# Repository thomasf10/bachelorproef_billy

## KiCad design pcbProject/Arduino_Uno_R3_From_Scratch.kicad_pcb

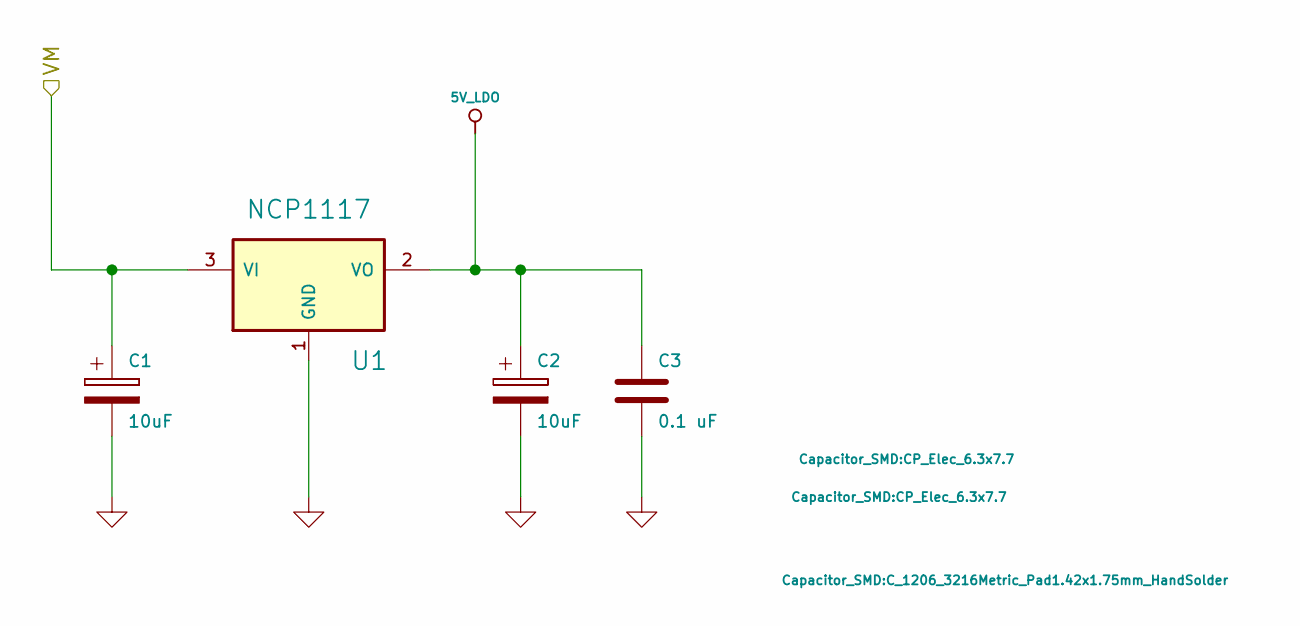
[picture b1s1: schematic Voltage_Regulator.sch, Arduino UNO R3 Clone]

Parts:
C1, C2: 10uF; CP_Elec_6.3x7.7
C3: 0.1 uF; C_1206_3216Metric_Pad1.42x1.75mm_HandSolder
U1: NCP1117; SOT223

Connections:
5V_LDO: C2.1, C3.1, U1.2 (VO); also elsewhere on the board
/DecouplingCapacitors/VM: C1.1, U1.3 (VI); also elsewhere on the board
GND: C1.2, C2.2, C3.2, U1.1 (GND); also elsewhere on the board

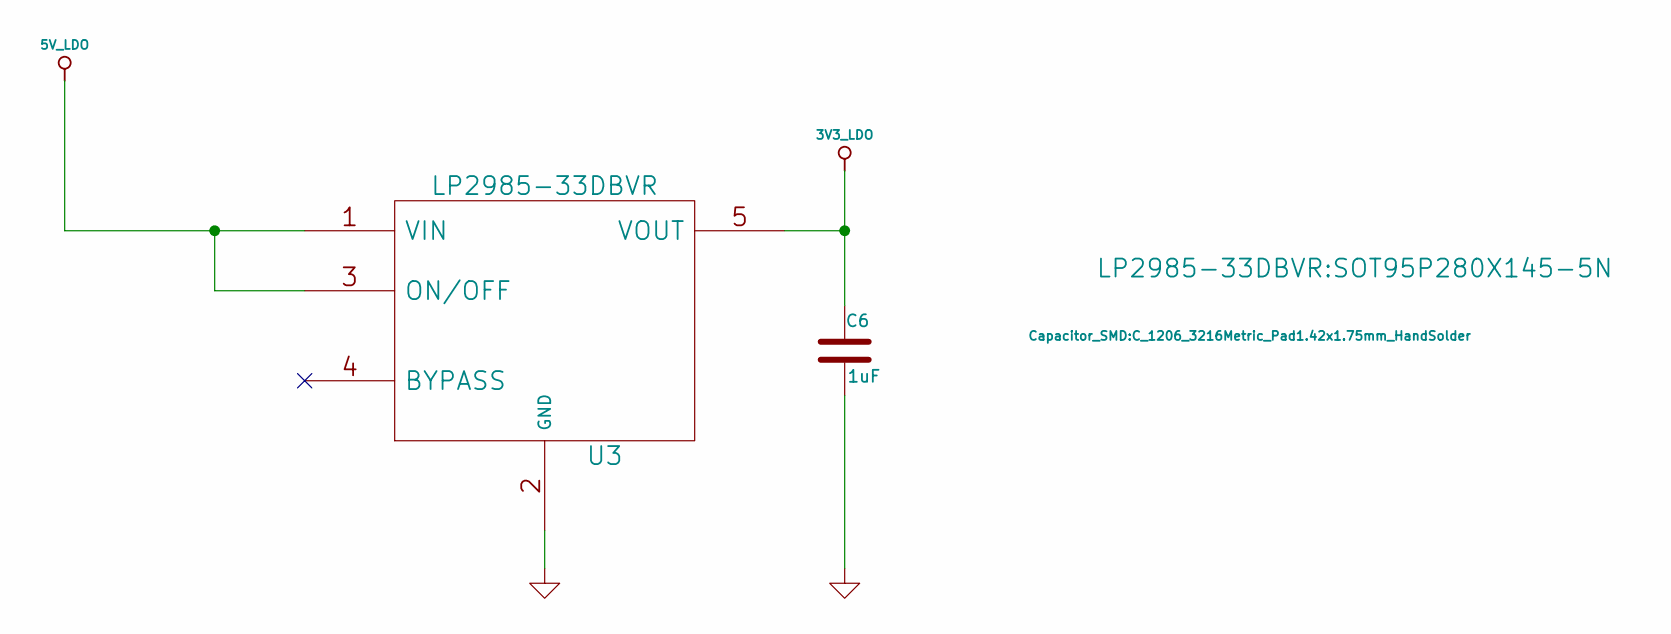
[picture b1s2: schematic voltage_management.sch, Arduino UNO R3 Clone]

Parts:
C6: 1uF; C_1206_3216Metric_Pad1.42x1.75mm_HandSolder
U3: LP2985-33DBVR; SOT95P280X145-5N

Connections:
3V3_LDO: C6.1, U3.5 (VOUT); also elsewhere on the board
5V_LDO: U3.1 (VIN), U3.3 (ON/OFF); also elsewhere on the board
GND: C6.2, U3.2 (GND); also elsewhere on the board

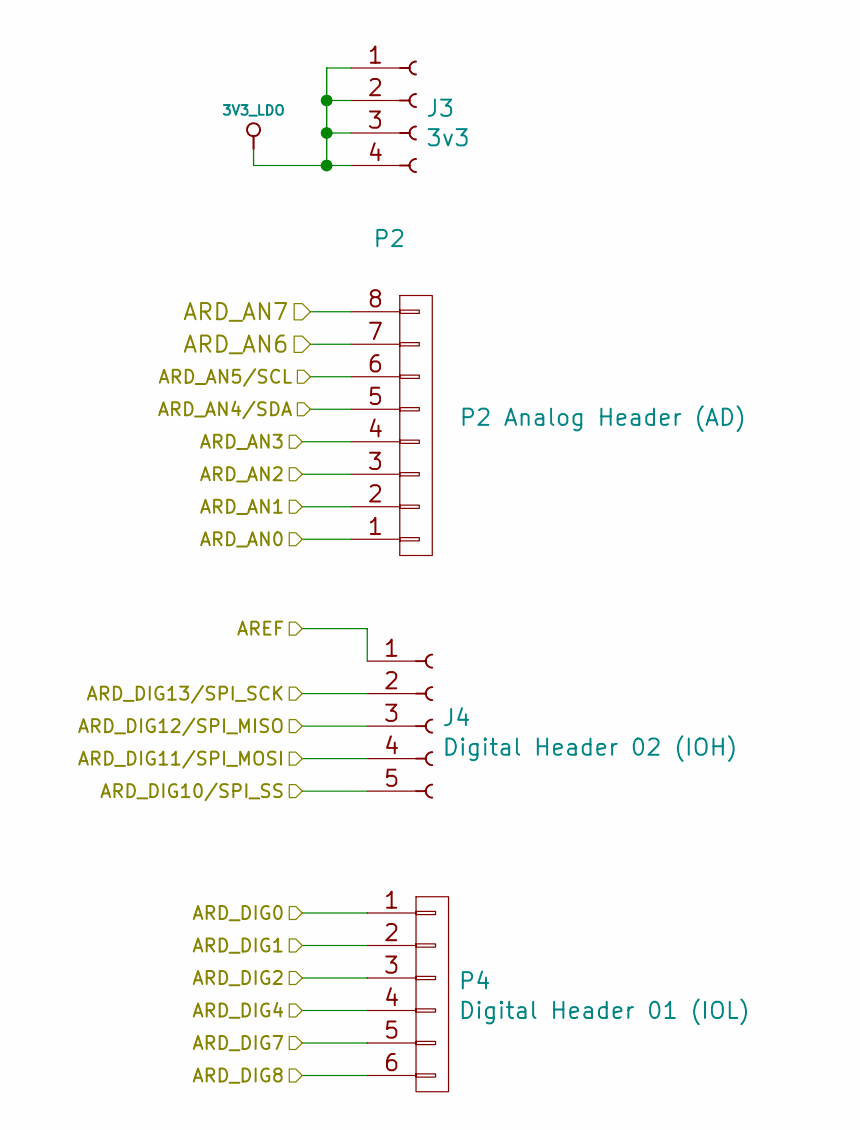
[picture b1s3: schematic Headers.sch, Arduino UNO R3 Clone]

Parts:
J3: 3v3; PinSocket_1x04_P2.54mm_Vertical
J4: Digital Header 02 (IOH); PinSocket_1x05_P2.54mm_Vertical
P2: P2 Analog Header (AD); PinSocket_1x08_P2.54mm_Vertical
P4: Digital Header 01 (IOL); PinSocket_1x06_P2.54mm_Vertical

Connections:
3V3_LDO: J3.1, J3.2, J3.3, J3.4; also elsewhere on the board
328P_ICSP_MISO: J4.3; also elsewhere on the board
328P_ICSP_MOSI: J4.4; also elsewhere on the board
328P_ICSP_SCK: J4.2; also elsewhere on the board
/ATMEGA328P/ARD_AN0: P2.1; also elsewhere on the board
/ATMEGA328P/ARD_AN1: P2.2; also elsewhere on the board
/ATMEGA328P/ARD_AN2: P2.3; also elsewhere on the board
/ATMEGA328P/ARD_AN3: P2.4; also elsewhere on the board
/ATMEGA328P/ARD_AN4/SDA: P2.5; also elsewhere on the board
/ATMEGA328P/ARD_AN5/SCL: P2.6; also elsewhere on the board
/ATMEGA328P/ARD_AN6: P2.7; also elsewhere on the board
/ATMEGA328P/ARD_AN7: P2.8; also elsewhere on the board
/ATMEGA328P/ARD_DIG0: P4.1; also elsewhere on the board
/ATMEGA328P/ARD_DIG1: P4.2; also elsewhere on the board
/ATMEGA328P/ARD_DIG2: P4.3; also elsewhere on the board
/ATMEGA328P/ARD_DIG4: P4.4; also elsewhere on the board
/ATMEGA328P/ARD_DIG7: P4.5; also elsewhere on the board
/ATMEGA328P/ARD_DIG8: P4.6; also elsewhere on the board
/ATMEGA328P/ARD_DIG10/SPI_SS: J4.5; also elsewhere on the board
/ATMEGA328P/AREF: J4.1; also elsewhere on the board

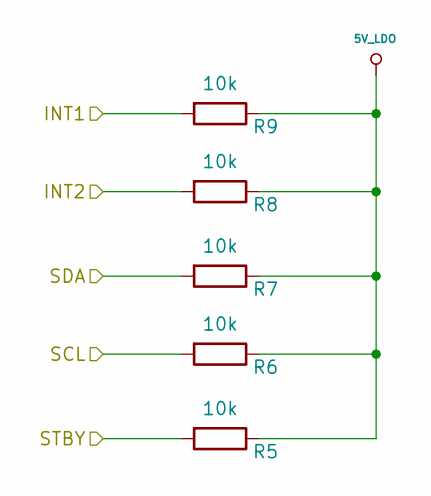
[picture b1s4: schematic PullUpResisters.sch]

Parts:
R5, R6, R7, R8, R9: 10k; R_1206_3216Metric_Pad1.42x1.75mm_HandSolder

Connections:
5V_LDO: R5.1, R6.1, R7.1, R8.1, R9.1; also elsewhere on the board
/ATMEGA328P/ARD_AN4/SDA: R7.2; also elsewhere on the board
/ATMEGA328P/ARD_AN5/SCL: R6.2; also elsewhere on the board
/IOExpander/INT1: R9.2; also elsewhere on the board
/IOExpander/INT2: R8.2; also elsewhere on the board
/MotorDriver/STBY: R5.2; also elsewhere on the board

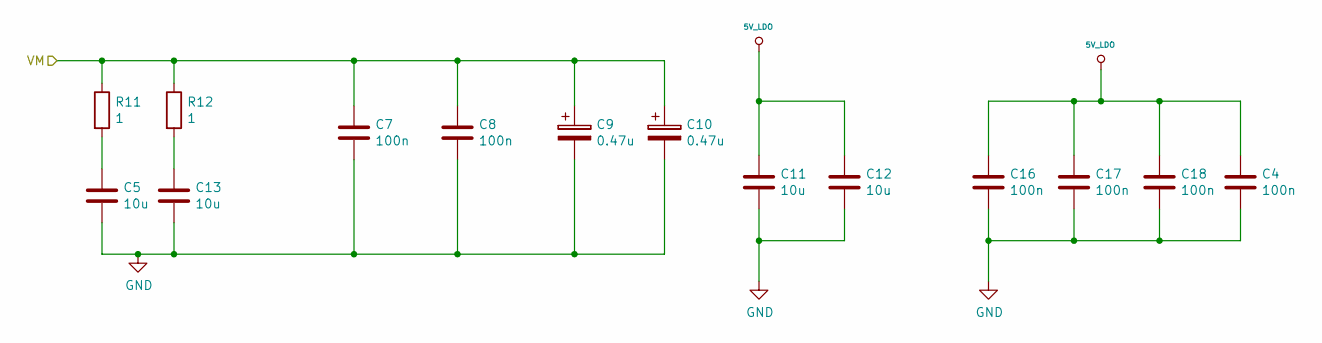
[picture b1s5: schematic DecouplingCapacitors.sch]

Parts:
C4, C7, C8, C16, C17, C18: 100n; C_1206_3216Metric_Pad1.42x1.75mm_HandSolder
C5, C11, C12, C13: 10u; C_1206_3216Metric_Pad1.42x1.75mm_HandSolder
C9, C10: 0.47u; CP_Elec_4x3.9
R11, R12: 1; R_1206_3216Metric_Pad1.42x1.75mm_HandSolder

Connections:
5V_LDO: C4.1, C11.1, C12.1, C16.1, C17.1, C18.1; also elsewhere on the board
/DecouplingCapacitors/VM: C7.1, C8.1, C9.1, C10.1, R11.1, R12.1; also elsewhere on the board
GND: C4.2, C5.2, C7.2, C8.2, C9.2, C10.2, C11.2, C12.2, C13.2, C16.2, C17.2, C18.2; also elsewhere on the board
unnamed: C5.1, R11.2
unnamed: C13.1, R12.2

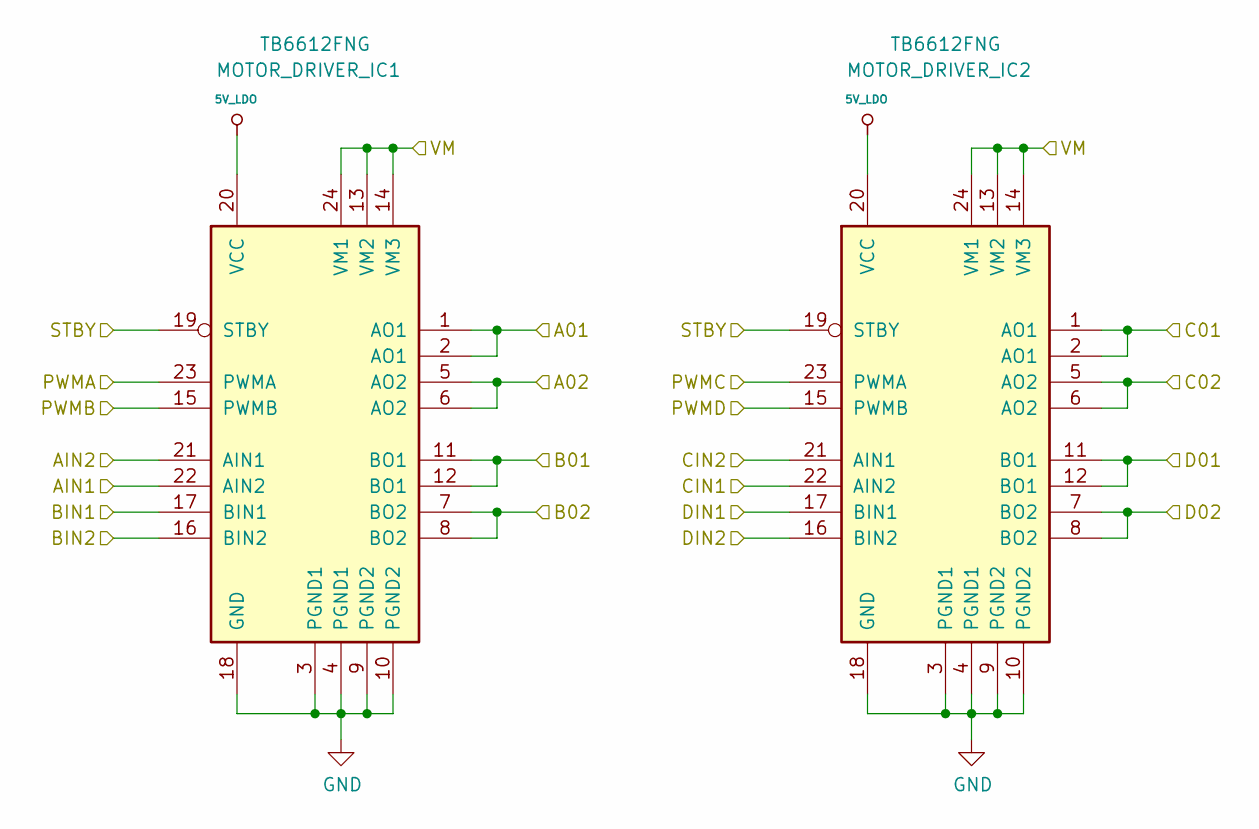
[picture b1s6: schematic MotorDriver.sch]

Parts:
MOTOR_DRIVER_IC1, MOTOR_DRIVER_IC2: TB6612FNG; SSOP-24_5.3x8.2mm_P0.65mm

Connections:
5V_LDO: MOTOR_DRIVER_IC1.20 (VCC), MOTOR_DRIVER_IC2.20 (VCC); also elsewhere on the board
/ATMEGA328P/ARD_DIG3: MOTOR_DRIVER_IC2.15 (PWMB); also elsewhere on the board
/ATMEGA328P/ARD_DIG5: MOTOR_DRIVER_IC2.23 (PWMA); also elsewhere on the board
/ATMEGA328P/ARD_DIG6: MOTOR_DRIVER_IC1.15 (PWMB); also elsewhere on the board
/ATMEGA328P/ARD_DIG9: MOTOR_DRIVER_IC1.23 (PWMA); also elsewhere on the board
/DecouplingCapacitors/VM: MOTOR_DRIVER_IC1.13 (VM2), MOTOR_DRIVER_IC1.14 (VM3), MOTOR_DRIVER_IC1.24 (VM1), MOTOR_DRIVER_IC2.13 (VM2), MOTOR_DRIVER_IC2.14 (VM3), MOTOR_DRIVER_IC2.24 (VM1); also elsewhere on the board
/IOExpander/AIN1: MOTOR_DRIVER_IC1.22 (AIN2); also elsewhere on the board
/IOExpander/AIN2: MOTOR_DRIVER_IC1.21 (AIN1); also elsewhere on the board
/IOExpander/BIN1: MOTOR_DRIVER_IC1.17 (BIN1); also elsewhere on the board
/IOExpander/BIN2: MOTOR_DRIVER_IC1.16 (BIN2); also elsewhere on the board
/IOExpander/CIN1: MOTOR_DRIVER_IC2.22 (AIN2); also elsewhere on the board
/IOExpander/CIN2: MOTOR_DRIVER_IC2.21 (AIN1); also elsewhere on the board
/IOExpander/DIN1: MOTOR_DRIVER_IC2.17 (BIN1); also elsewhere on the board
/IOExpander/DIN2: MOTOR_DRIVER_IC2.16 (BIN2); also elsewhere on the board
/MotorDriver/A01: MOTOR_DRIVER_IC1.1 (AO1), MOTOR_DRIVER_IC1.2 (AO1); also elsewhere on the board
/MotorDriver/A02: MOTOR_DRIVER_IC1.5 (AO2), MOTOR_DRIVER_IC1.6 (AO2); also elsewhere on the board
/MotorDriver/B01: MOTOR_DRIVER_IC1.11 (BO1), MOTOR_DRIVER_IC1.12 (BO1); also elsewhere on the board
/MotorDriver/B02: MOTOR_DRIVER_IC1.7 (BO2), MOTOR_DRIVER_IC1.8 (BO2); also elsewhere on the board
/MotorDriver/C01: MOTOR_DRIVER_IC2.1 (AO1), MOTOR_DRIVER_IC2.2 (AO1); also elsewhere on the board
/MotorDriver/C02: MOTOR_DRIVER_IC2.5 (AO2), MOTOR_DRIVER_IC2.6 (AO2); also elsewhere on the board
/MotorDriver/D01: MOTOR_DRIVER_IC2.11 (BO1), MOTOR_DRIVER_IC2.12 (BO1); also elsewhere on the board
/MotorDriver/D02: MOTOR_DRIVER_IC2.7 (BO2), MOTOR_DRIVER_IC2.8 (BO2); also elsewhere on the board
/MotorDriver/STBY: MOTOR_DRIVER_IC1.19 (STBY), MOTOR_DRIVER_IC2.19 (STBY); also elsewhere on the board
GND: MOTOR_DRIVER_IC1.3 (PGND1), MOTOR_DRIVER_IC1.4 (PGND1), MOTOR_DRIVER_IC1.9 (PGND2), MOTOR_DRIVER_IC1.10 (PGND2), MOTOR_DRIVER_IC1.18 (GND), MOTOR_DRIVER_IC2.3 (PGND1), MOTOR_DRIVER_IC2.4 (PGND1), MOTOR_DRIVER_IC2.9 (PGND2), MOTOR_DRIVER_IC2.10 (PGND2), MOTOR_DRIVER_IC2.18 (GND); also elsewhere on the board

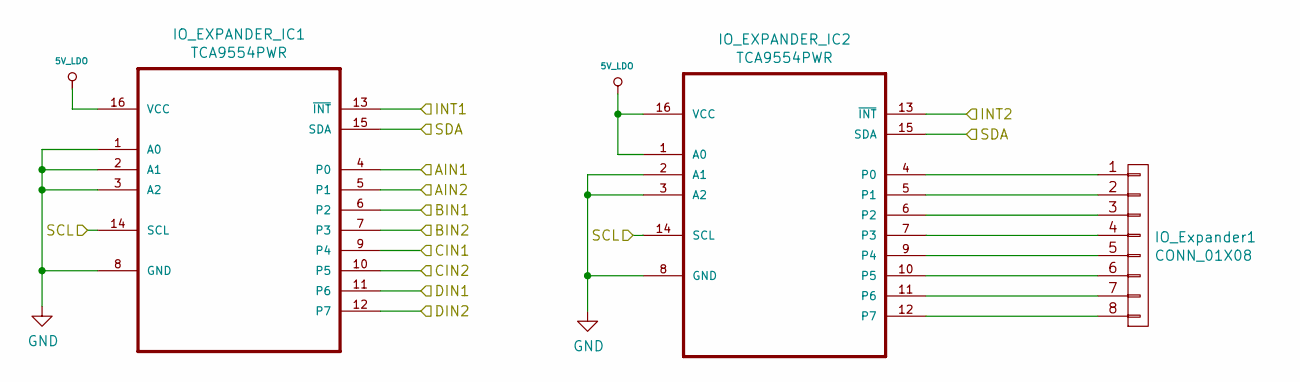
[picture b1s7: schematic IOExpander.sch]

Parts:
IO_EXPANDER_IC1, IO_EXPANDER_IC2: TCA9554PWR; SOP65P640X120-16N
IO_Expander1: CONN_01X08

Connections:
5V_LDO: IO_EXPANDER_IC1.16 (VCC), IO_EXPANDER_IC2.1 (A0), IO_EXPANDER_IC2.16 (VCC); also elsewhere on the board
/ATMEGA328P/ARD_AN4/SDA: IO_EXPANDER_IC1.15 (SDA), IO_EXPANDER_IC2.15 (SDA); also elsewhere on the board
/ATMEGA328P/ARD_AN5/SCL: IO_EXPANDER_IC1.14 (SCL), IO_EXPANDER_IC2.14 (SCL); also elsewhere on the board
/IOExpander/AIN1: IO_EXPANDER_IC1.4 (P0); also elsewhere on the board
/IOExpander/AIN2: IO_EXPANDER_IC1.5 (P1); also elsewhere on the board
/IOExpander/BIN1: IO_EXPANDER_IC1.6 (P2); also elsewhere on the board
/IOExpander/BIN2: IO_EXPANDER_IC1.7 (P3); also elsewhere on the board
/IOExpander/CIN1: IO_EXPANDER_IC1.9 (P4); also elsewhere on the board
/IOExpander/CIN2: IO_EXPANDER_IC1.10 (P5); also elsewhere on the board
/IOExpander/DIN1: IO_EXPANDER_IC1.11 (P6); also elsewhere on the board
/IOExpander/DIN2: IO_EXPANDER_IC1.12 (P7); also elsewhere on the board
/IOExpander/INT1: IO_EXPANDER_IC1.13 (~INT); also elsewhere on the board
/IOExpander/INT2: IO_EXPANDER_IC2.13 (~INT); also elsewhere on the board
GND: IO_EXPANDER_IC1.1 (A0), IO_EXPANDER_IC1.2 (A1), IO_EXPANDER_IC1.3 (A2), IO_EXPANDER_IC1.8 (GND), IO_EXPANDER_IC2.2 (A1), IO_EXPANDER_IC2.3 (A2), IO_EXPANDER_IC2.8 (GND); also elsewhere on the board
unnamed 51: IO_EXPANDER_IC2.4 (P0), IO_Expander1.1; also elsewhere on the board
unnamed 52: IO_EXPANDER_IC2.5 (P1), IO_Expander1.2; also elsewhere on the board
unnamed 53: IO_EXPANDER_IC2.6 (P2), IO_Expander1.3; also elsewhere on the board
unnamed 54: IO_EXPANDER_IC2.7 (P3), IO_Expander1.4; also elsewhere on the board
unnamed 55: IO_EXPANDER_IC2.9 (P4), IO_Expander1.5; also elsewhere on the board
unnamed 56: IO_EXPANDER_IC2.10 (P5), IO_Expander1.6; also elsewhere on the board
unnamed 57: IO_EXPANDER_IC2.11 (P6), IO_Expander1.7; also elsewhere on the board
unnamed 58: IO_EXPANDER_IC2.12 (P7), IO_Expander1.8; also elsewhere on the board

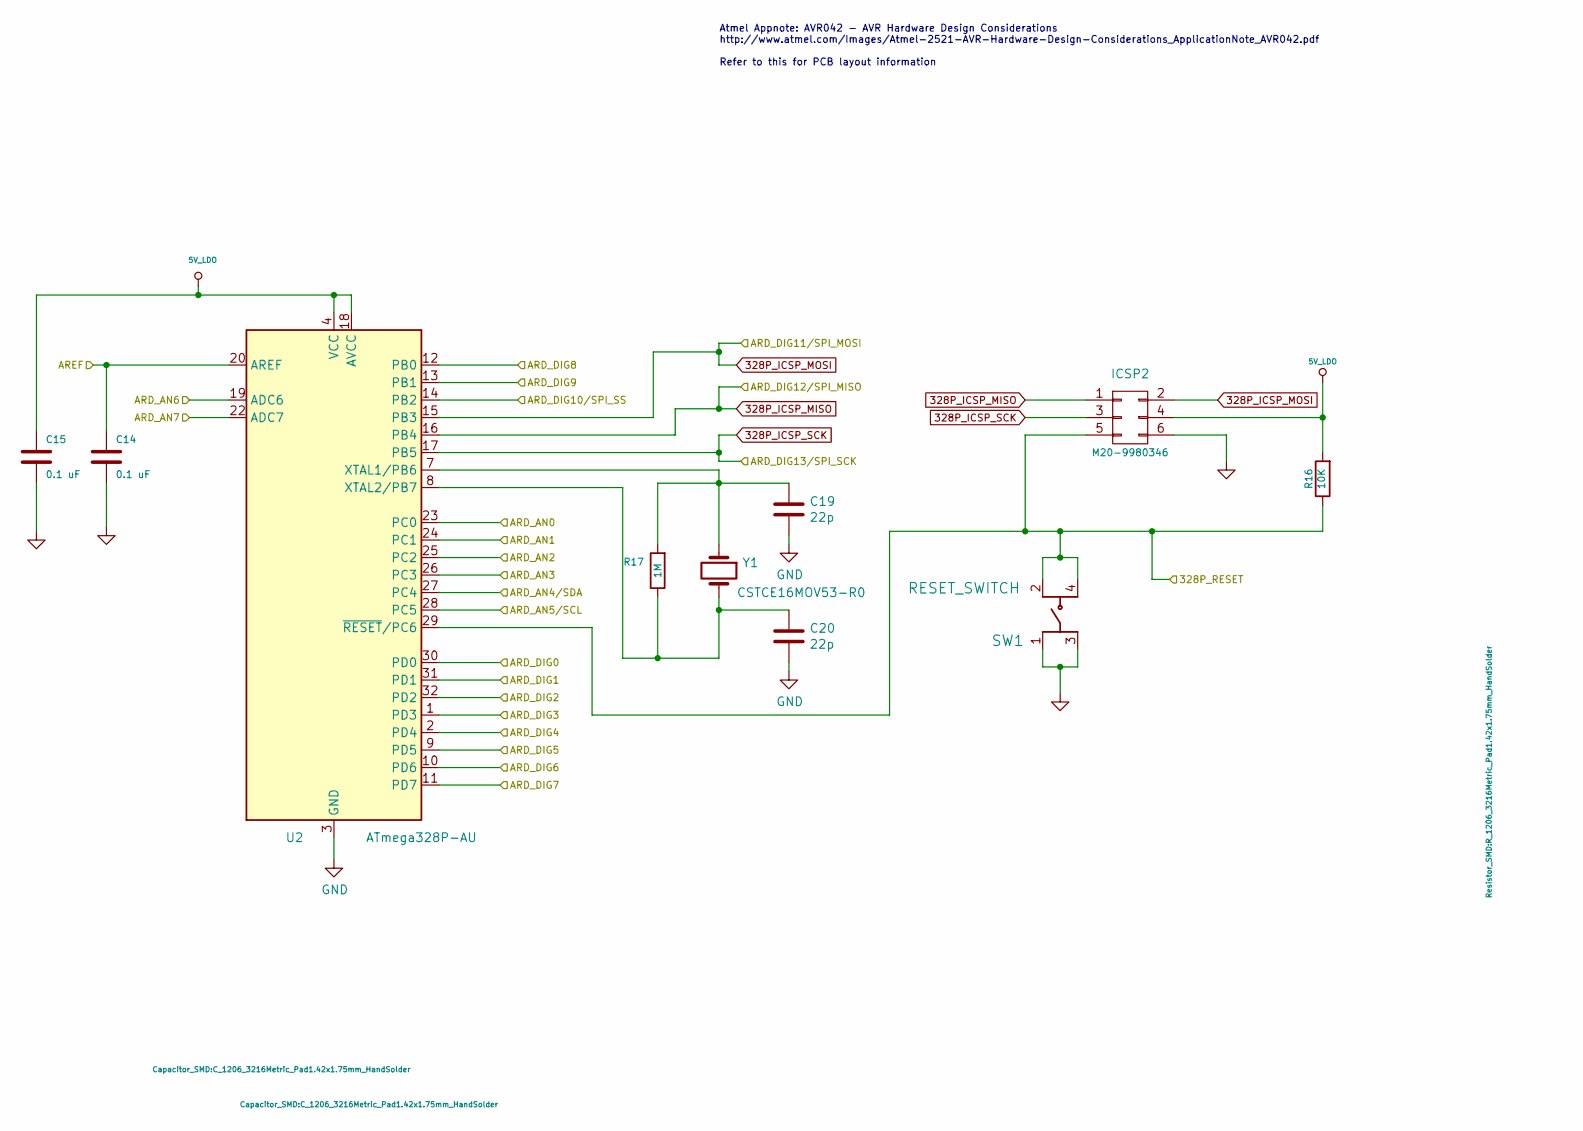
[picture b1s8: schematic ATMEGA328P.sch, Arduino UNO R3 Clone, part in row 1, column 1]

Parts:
C14, C15: 0.1 uF; C_1206_3216Metric_Pad1.42x1.75mm_HandSolder
C19, C20: 22p; C_0805_2012Metric_Pad1.15x1.40mm_HandSolder
ICSP2: M20-9980346; PinSocket_2x03_P2.54mm_Vertical
R16: 10K; R_1206_3216Metric_Pad1.42x1.75mm_HandSolder
R17: 1M; R_1206_3216Metric_Pad1.42x1.75mm_HandSolder
SW1: RESET_SWITCH; SW_SPST_PTS645_aangepast
U2: ATmega328P-AU; TQFP-32_7x7mm_P0.8mm
Y1: CSTCE16MOV53-R0; Crystal_SMD_HC49-SD

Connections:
5V_LDO: C15.1, ICSP2.4, R16.2, U2.4 (VCC), U2.6 (VCC), U2.18 (AVCC); also elsewhere on the board
328P_ICSP_MISO: ICSP2.1, U2.16 (PB4); also elsewhere on the board
328P_ICSP_MOSI: ICSP2.2, U2.15 (PB3); also elsewhere on the board
328P_ICSP_SCK: ICSP2.3, U2.17 (PB5); also elsewhere on the board
/ATMEGA328P/328P_RESET: ICSP2.5, R16.1, SW1.2, SW1.4, U2.29 (~RESET~/PC6)
/ATMEGA328P/ARD_AN0: U2.23 (PC0); also elsewhere on the board
/ATMEGA328P/ARD_AN1: U2.24 (PC1); also elsewhere on the board
/ATMEGA328P/ARD_AN2: U2.25 (PC2); also elsewhere on the board
/ATMEGA328P/ARD_AN3: U2.26 (PC3); also elsewhere on the board
/ATMEGA328P/ARD_AN4/SDA: U2.27 (PC4); also elsewhere on the board
/ATMEGA328P/ARD_AN5/SCL: U2.28 (PC5); also elsewhere on the board
/ATMEGA328P/ARD_AN6: U2.19 (ADC6); also elsewhere on the board
/ATMEGA328P/ARD_AN7: U2.22 (ADC7); also elsewhere on the board
/ATMEGA328P/ARD_DIG0: U2.30 (PD0); also elsewhere on the board
/ATMEGA328P/ARD_DIG1: U2.31 (PD1); also elsewhere on the board
/ATMEGA328P/ARD_DIG2: U2.32 (PD2); also elsewhere on the board
/ATMEGA328P/ARD_DIG3: U2.1 (PD3); also elsewhere on the board
/ATMEGA328P/ARD_DIG4: U2.2 (PD4); also elsewhere on the board
/ATMEGA328P/ARD_DIG5: U2.9 (PD5); also elsewhere on the board
/ATMEGA328P/ARD_DIG6: U2.10 (PD6); also elsewhere on the board
/ATMEGA328P/ARD_DIG7: U2.11 (PD7); also elsewhere on the board
/ATMEGA328P/ARD_DIG8: U2.12 (PB0); also elsewhere on the board
/ATMEGA328P/ARD_DIG9: U2.13 (PB1); also elsewhere on the board
/ATMEGA328P/ARD_DIG10/SPI_SS: U2.14 (PB2); also elsewhere on the board
/ATMEGA328P/AREF: C14.1, U2.20 (AREF); also elsewhere on the board
GND: C14.2, C15.2, C19.2, C20.2, ICSP2.6, SW1.1, SW1.3, U2.3 (GND), U2.5 (GND), U2.21 (GND); also elsewhere on the board
unnamed: C19.1, R17.2, U2.7 (XTAL1/PB6), Y1.1
unnamed: C20.1, R17.1, U2.8 (XTAL2/PB7), Y1.2

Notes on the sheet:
Atmel Appnote: AVR042 - AVR Hardware Design Considerations http://www.atmel.com/Images/Atmel-2521-AVR-Hardware-Design-Considerations_ApplicationNote_AVR042.pdf Refer to this for PCB layout information

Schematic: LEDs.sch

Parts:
LED1: GREEN; LED_0805_2012Metric
R10: 470; R_1206_3216Metric_Pad1.42x1.75mm_HandSolder

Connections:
GND: R10.1; also elsewhere on the board
unnamed 59: LED1.1 (K), R10.2; also elsewhere on the board

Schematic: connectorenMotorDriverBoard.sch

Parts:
GND1: 12V; degson-DG306-5.0-02P
J1: INTERRUPT; PinSocket_1x03_P2.54mm_Vertical
J2: STBY; PinSocket_1x03_P2.54mm_Vertical
MA-1A1: MA-2B; degson-DG306-5.0-02P
MB-1A1: MB-2B; degson-DG306-5.0-02P
MC-1A1: MC-2B; degson-DG306-5.0-02P
MD-1A1: MD-2B; degson-DG306-5.0-02P
P5: GND; PinSocket_1x08_P2.54mm_Vertical
P6: +5V; PinSocket_1x08_P2.54mm_Vertical

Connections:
5V_LDO: J2.2, P6.1, P6.2, P6.3, P6.4, P6.5, P6.6, P6.7, P6.8; also elsewhere on the board
/IOExpander/INT1: J1.2; also elsewhere on the board
/IOExpander/INT2: J1.3; also elsewhere on the board
/MotorDriver/A01: MA-1A1.1; also elsewhere on the board
/MotorDriver/A02: MA-1A1.2; also elsewhere on the board
/MotorDriver/B01: MB-1A1.1; also elsewhere on the board
/MotorDriver/B02: MB-1A1.2; also elsewhere on the board
/MotorDriver/C01: MC-1A1.1; also elsewhere on the board
/MotorDriver/C02: MC-1A1.2; also elsewhere on the board
/MotorDriver/D01: MD-1A1.1; also elsewhere on the board
/MotorDriver/D02: MD-1A1.2; also elsewhere on the board
/MotorDriver/STBY: J2.3; also elsewhere on the board
GND: GND1.1, J1.1, J2.1, P5.1, P5.2, P5.3, P5.4, P5.5, P5.6, P5.7, P5.8; also elsewhere on the board

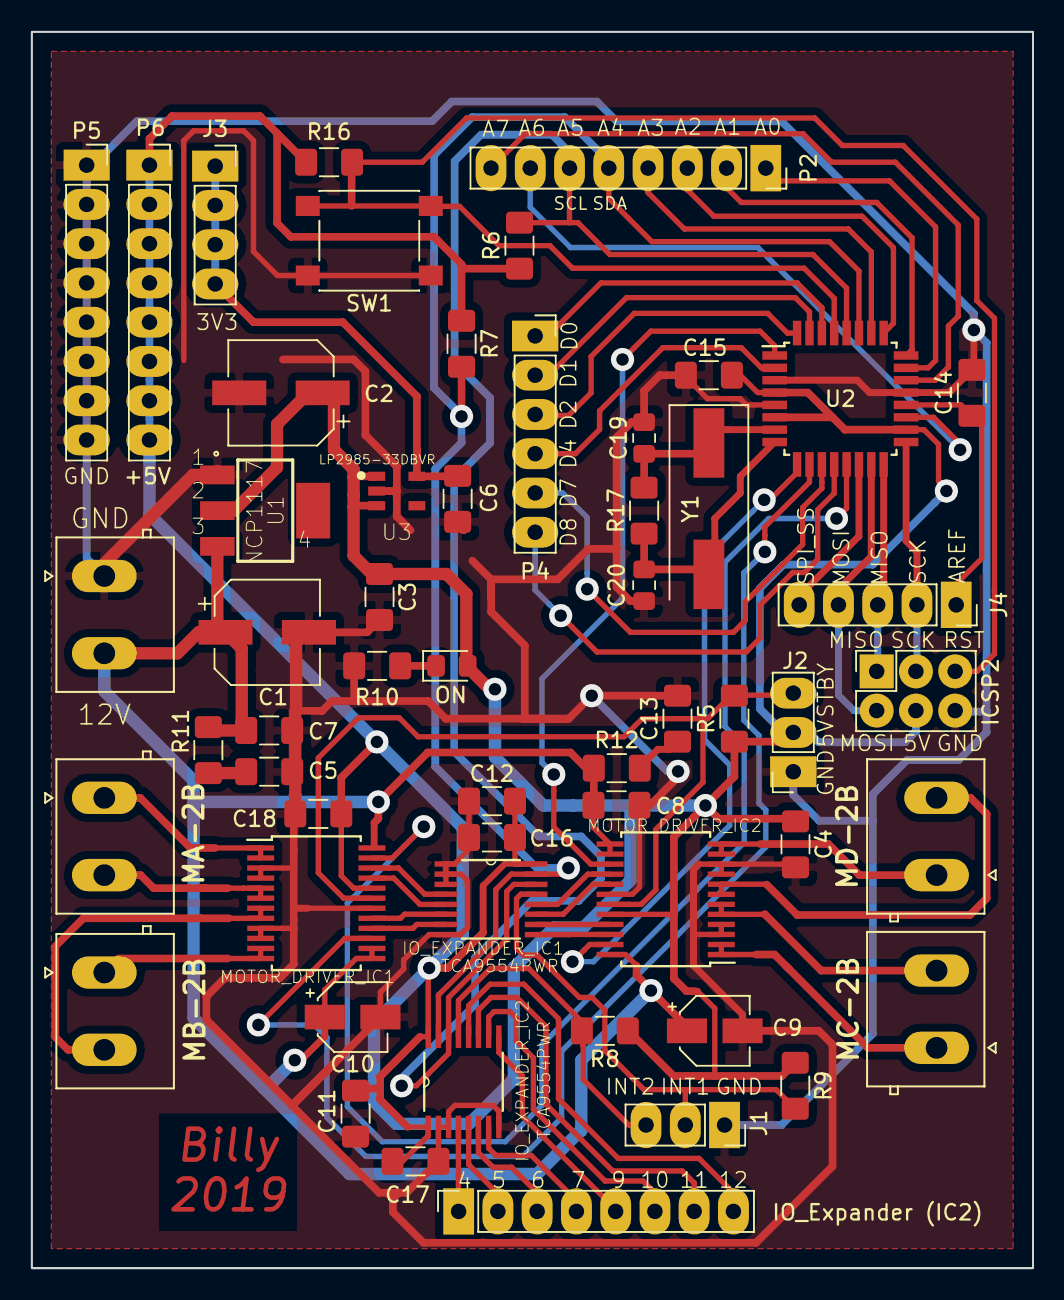
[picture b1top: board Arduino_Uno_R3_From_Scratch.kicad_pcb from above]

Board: 2 copper layers, 64.8 x 80.0 mm, 55 parts (0 on the bottom side), 60 nets.

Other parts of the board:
GND: 12V; degson-DG306-5.0-02P
IO_Expander (IC2): CONN_01X08; PinSocket_1x08_P2.54mm_Vertical
ON: GREEN; LED_0805_2012Metric_Pad1.15x1.40mm_HandSolder

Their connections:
5V_LDO: ON.2; also elsewhere on the board
/DecouplingCapacitors/VM: GND.2; also elsewhere on the board
GND: GND.1; also elsewhere on the board
unnamed 51: IO_Expander (IC2).1; also elsewhere on the board
unnamed 52: IO_Expander (IC2).2; also elsewhere on the board
unnamed 53: IO_Expander (IC2).3; also elsewhere on the board
unnamed 54: IO_Expander (IC2).4; also elsewhere on the board
unnamed 55: IO_Expander (IC2).5; also elsewhere on the board
unnamed 56: IO_Expander (IC2).6; also elsewhere on the board
unnamed 57: IO_Expander (IC2).7; also elsewhere on the board
unnamed 58: IO_Expander (IC2).8; also elsewhere on the board
unnamed 59: ON.1; also elsewhere on the board

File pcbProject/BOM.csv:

"Id";"Designator";"Package";"Quantity";"Designation";"Supplier and ref";
1;"ON";"LED_0805_2012Metric_Pad1.15x1.40mm_HandSolder";1;"GREEN";;;
2;"Y1";"Crystal_SMD_HC49-SD";1;"CSTCE16MOV53-R0";;;
3;"C5,C11,C12,C13";"C_1206_3216Metric_Pad1.42x1.75mm_HandSolder";4;"10u";;;
4;"MD-1A1";"degson-DG306-5.0-02P";1;"MD-2B";;;
5;"SW1";"SW_SPST_PTS645_aangepast";1;"RESET_SWITCH";;;
6;"C1,C2";"CP_Elec_6.3x7.7";2;"10uF";;;
7;"C9,C10";"CP_Elec_4x3.9";2;"0.47u";;;
8;"GND";"degson-DG306-5.0-02P";1;"12V";;;
9;"ICSP2";"PinSocket_2x03_P2.54mm_Vertical";1;"M20-9980346";;;
10;"IO_Expander (IC2)";"PinSocket_1x08_P2.54mm_Vertical";1;"CONN_01X08";;;
11;"IO_EXPANDER_IC1,IO_EXPANDER_IC2";"SOP65P640X120-16N";2;"TCA9554PWR";;;
12;"J1";"PinSocket_1x03_P2.54mm_Vertical";1;"INTERRUPT";;;
13;"J2";"PinSocket_1x03_P2.54mm_Vertical";1;"STBY";;;
14;"MA-1A1";"degson-DG306-5.0-02P";1;"MA-2B";;;
15;"MB-1A1";"degson-DG306-5.0-02P";1;"MB-2B";;;
16;"MC-1A1";"degson-DG306-5.0-02P";1;"MC-2B";;;
17;"MOTOR_DRIVER_IC1,MOTOR_DRIVER_IC2";"SSOP-24_5.3x8.2mm_P0.65mm";2;"TB6612FNG";;;
18;"P2";"PinSocket_1x08_P2.54mm_Vertical";1;"P2 Analog Header (AD)";;;
19;"P4";"PinSocket_1x06_P2.54mm_Vertical";1;"Digital Header 01 (IOL)";;;
20;"P5";"PinSocket_1x08_P2.54mm_Vertical";1;"GND";;;
21;"P6";"PinSocket_1x08_P2.54mm_Vertical";1;"+5V";;;
22;"U1";"SOT223";1;"NCP1117";;;
23;"U2";"TQFP-32_7x7mm_P0.8mm";1;"ATmega328P-AU";;;
24;"U3";"SOT95P280X145-5N";1;"LP2985-33DBVR";;;
25;"J3";"PinSocket_1x04_P2.54mm_Vertical";1;"3v3";;;
26;"J4";"PinSocket_1x05_P2.54mm_Vertical";1;"Digital Header 02 (IOH)";;;
27;"C3,C14,C15";"C_1206_3216Metric_Pad1.42x1.75mm_HandSolder";3;"0.1 uF";;;
28;"C4,C7,C8,C16,C17,C18";"C_1206_3216Metric_Pad1.42x1.75mm_HandSolder";6;"100n";;;
29;"C6";"C_1206_3216Metric_Pad1.42x1.75mm_HandSolder";1;"1uF";;;
30;"C19,C20";"C_0805_2012Metric_Pad1.15x1.40mm_HandSolder";2;"22p";;;
31;"R5,R6,R7,R8,R9";"R_1206_3216Metric_Pad1.42x1.75mm_HandSolder";5;"10k";;;
32;"R10";"R_1206_3216Metric_Pad1.42x1.75mm_HandSolder";1;"470";;;
33;"R11,R12";"R_1206_3216Metric_Pad1.42x1.75mm_HandSolder";2;"1";;;
34;"R16";"R_1206_3216Metric_Pad1.42x1.75mm_HandSolder";1;"10K";;;
35;"R17";"R_1206_3216Metric_Pad1.42x1.75mm_HandSolder";1;"1M";;;

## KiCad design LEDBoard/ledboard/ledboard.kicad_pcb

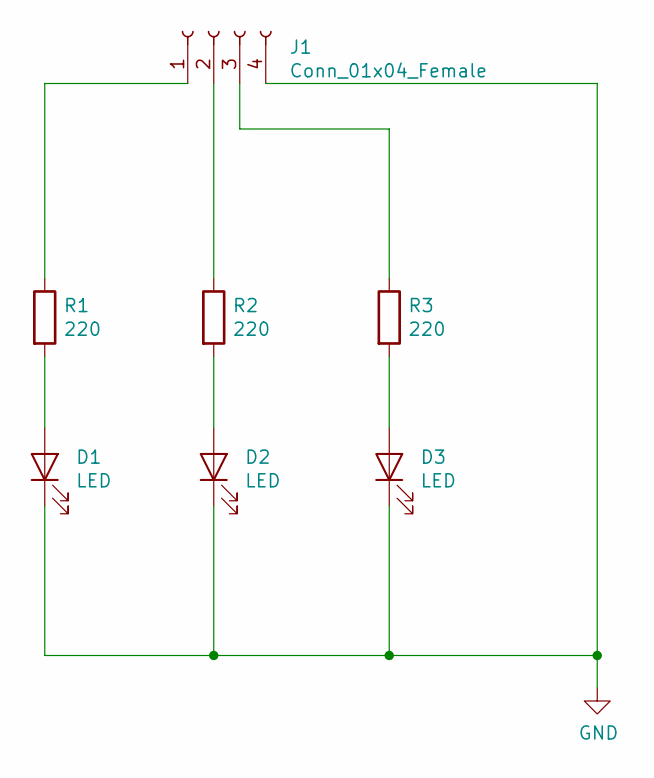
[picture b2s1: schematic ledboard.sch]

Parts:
D1, D2, D3: LED; LED_D3.0mm
J1: Conn_01x04_Female; PinSocket_1x04_P2.54mm_Vertical
R1, R2, R3: 220; R_Axial_DIN0207_L6.3mm_D2.5mm_P10.16mm_Horizontal

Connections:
GND: D1.1 (K), D2.1 (K), D3.1 (K), J1.4
unnamed: D1.2 (A), R1.2
unnamed: D2.2 (A), R2.2
unnamed: D3.2 (A), R3.2
unnamed: J1.1, R1.1
unnamed: J1.2, R2.1
unnamed: J1.3, R3.1

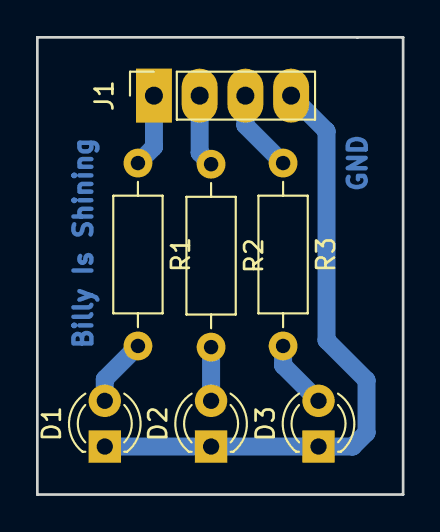
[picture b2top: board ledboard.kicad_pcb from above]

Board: 2 copper layers, 20.3 x 25.4 mm, 7 parts (0 on the bottom side), 7 nets.

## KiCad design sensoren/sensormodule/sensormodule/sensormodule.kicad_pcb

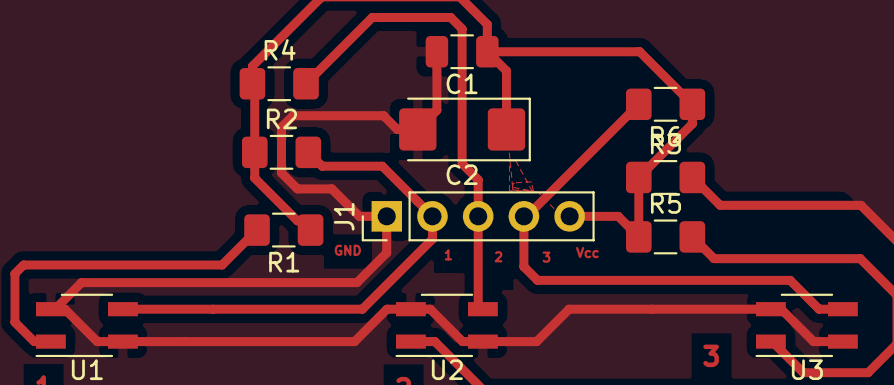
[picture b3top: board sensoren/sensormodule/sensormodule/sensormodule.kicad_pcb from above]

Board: 2 copper layers, 12 parts (0 on the bottom side), 8 nets.

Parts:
C1: 10n; C_1206_3216Metric
C2: 1u; CP_EIA-6032-15_Kemet-U
J1: Screw_Terminal_01x05; PinHeader_1x05_P2.54mm_Vertical
R1, R3, R5: 220; R_1206_3216Metric_Pad1.42x1.75mm_HandSolder
R2, R4, R6: 47k; R_1206_3216Metric_Pad1.42x1.75mm_HandSolder
U1, U2, U3: QRE1113; OnSemi_CASE100CY

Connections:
+5V: C1.1, C2.1, J1.5, R1.1, R2.1, R3.1, R4.1, R5.1, R6.1
GND: C1.2, C2.2, J1.1, U1.2, U1.4, U2.2, U2.4, U3.2, U3.4
unnamed: J1.2, R2.2, U1.3
unnamed: J1.3, R4.2, U2.3
unnamed: J1.4, R6.2, U3.3
unnamed: R1.2, U1.1
unnamed: R3.2, U2.1
unnamed: R5.2, U3.1

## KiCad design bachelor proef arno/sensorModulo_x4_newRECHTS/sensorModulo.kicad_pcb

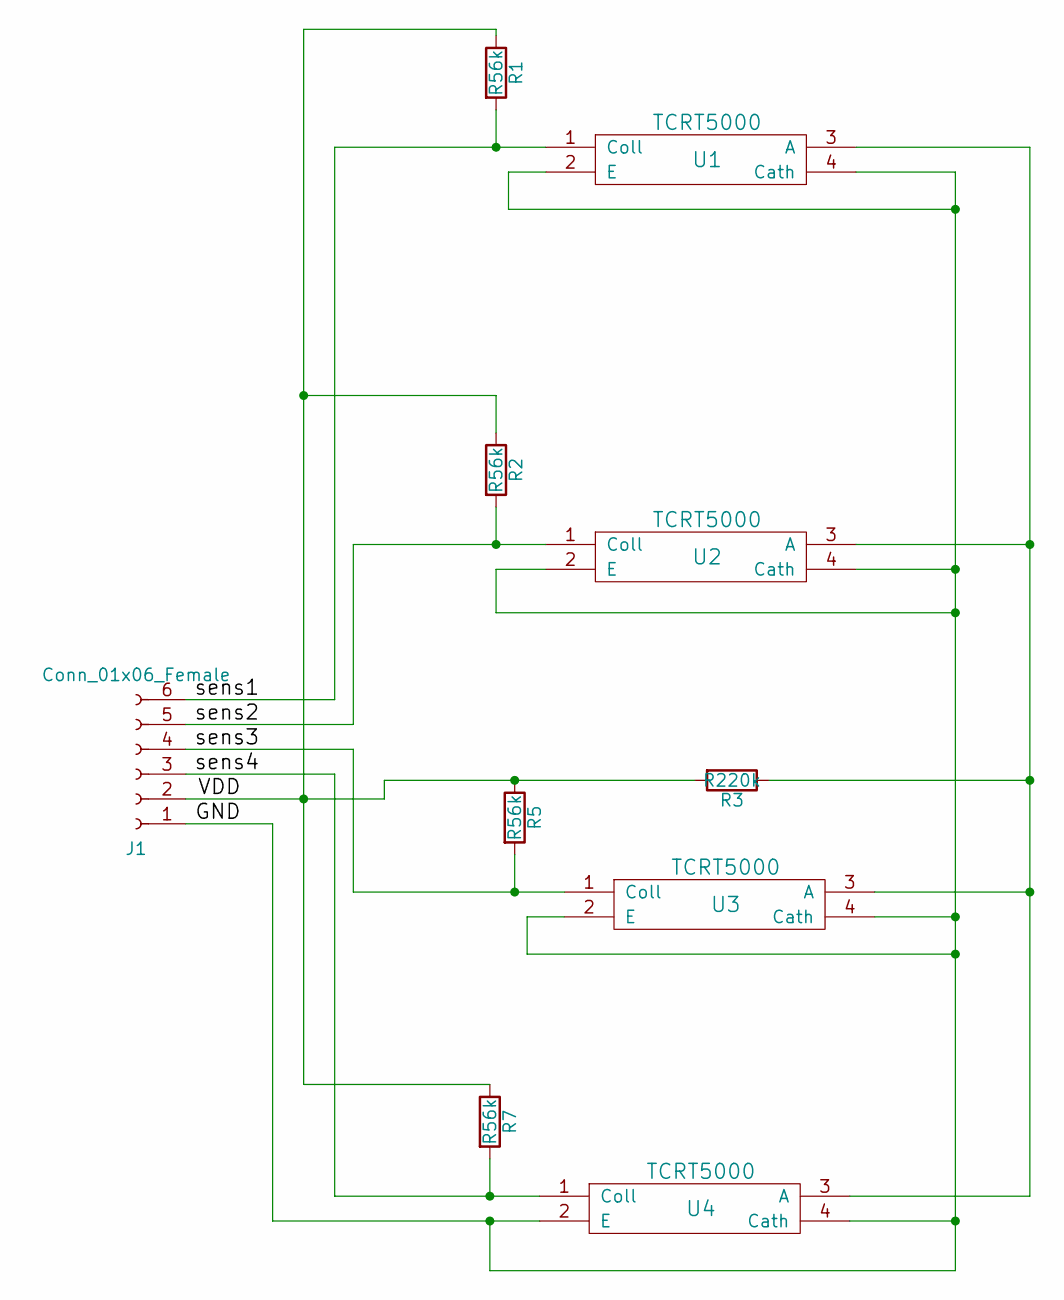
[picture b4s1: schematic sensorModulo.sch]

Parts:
J1: Conn_01x06_Female; Socket_Strip_Straight_1x06_Pitch2.54mm
R1, R2, R5, R7: R56k; R_Axial_DIN0207_L6.3mm_D2.5mm_P10.16mm_Horizontal
R3: R220k; R_Axial_DIN0207_L6.3mm_D2.5mm_P10.16mm_Horizontal
U1, U2, U3, U4: TCRT5000; TRTC5000

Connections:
/GND: J1.1, U1.2 (E), U1.4 (Cath), U2.2 (E), U2.4 (Cath), U3.2 (E), U3.4 (Cath), U4.2 (E), U4.4 (Cath)
/VDD: J1.2, R1.1, R2.1, R3.2, R5.1, R7.1
/sens1: J1.6, R1.2, U1.1 (Coll)
/sens2: J1.5, R2.2, U2.1 (Coll)
/sens3: J1.4, R5.2, U3.1 (Coll)
/sens4: J1.3, R7.2, U4.1 (Coll)
unnamed: R3.1, U1.3 (A), U2.3 (A), U3.3 (A), U4.3 (A)

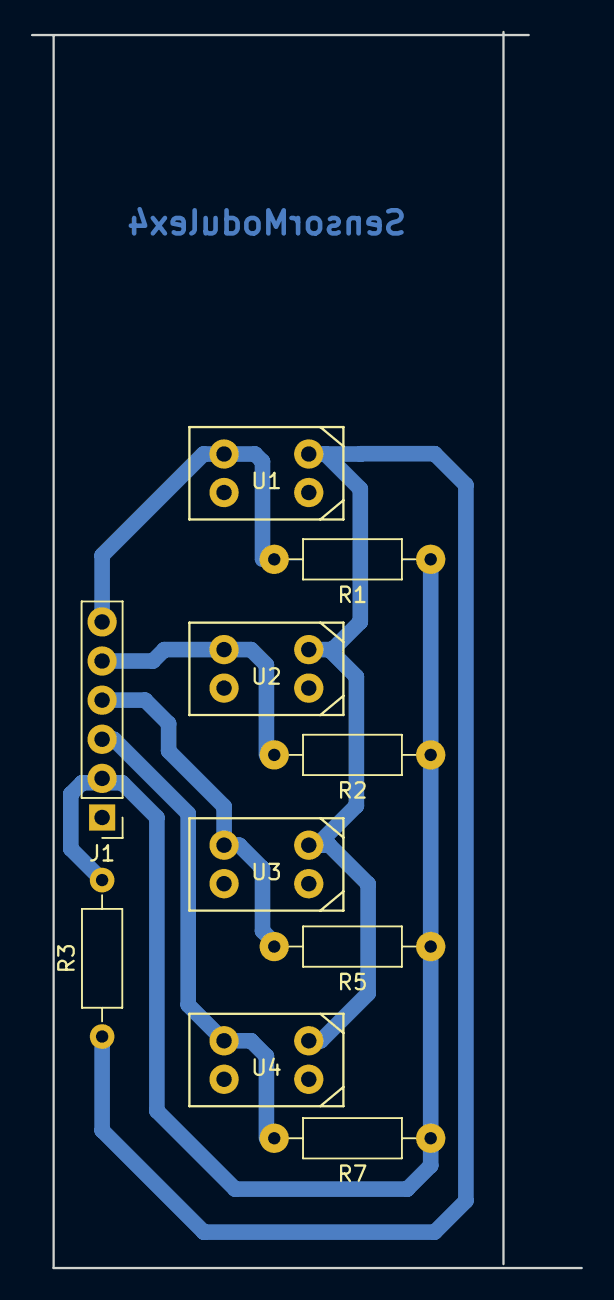
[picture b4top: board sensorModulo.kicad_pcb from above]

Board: 2 copper layers, 35.7 x 80.3 mm, 10 parts (0 on the bottom side), 7 nets.

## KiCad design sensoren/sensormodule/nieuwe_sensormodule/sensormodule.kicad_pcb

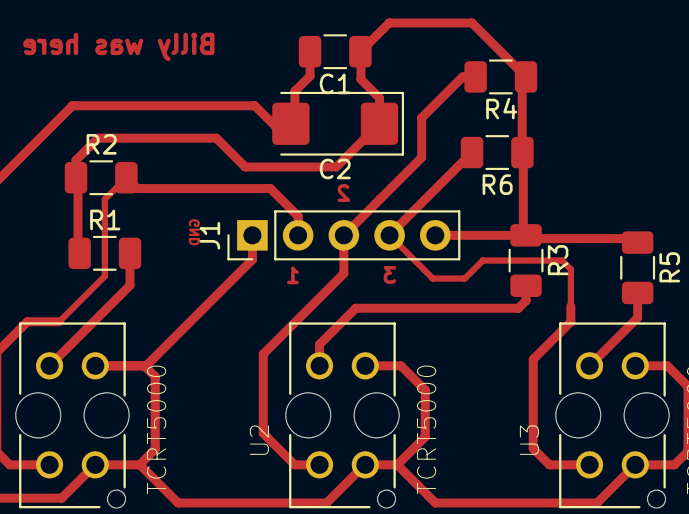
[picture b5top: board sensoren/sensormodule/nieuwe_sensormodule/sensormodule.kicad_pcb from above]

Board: 2 copper layers, 12 parts (0 on the bottom side), 8 nets.

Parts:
C1: 10n; C_1206_3216Metric
C2: 1u; CP_EIA-6032-15_Kemet-U
J1: Screw_Terminal_01x05; PinHeader_1x05_P2.54mm_Vertical
R1, R3, R5: 100; R_1206_3216Metric
R2, R4, R6: 4700; R_1206_3216Metric
U1, U2, U3: TCRT5000; OPTO_TCRT5000

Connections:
+5V: C1.1, C2.1, J1.5, R1.1, R2.1, R3.1, R4.1, R5.1, R6.1
GND: C1.2, C2.2, J1.1, U1.CATH, U1.E, U2.CATH, U2.E, U3.CATH, U3.E
unnamed: J1.2, R2.2, U1.COLL
unnamed: J1.3, R4.2, U2.COLL
unnamed: J1.4, R6.2, U3.COLL
unnamed: R1.2, U1.A
unnamed: R3.2, U2.A
unnamed: R5.2, U3.A
